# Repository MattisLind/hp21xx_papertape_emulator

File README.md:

# HP 21XX Paper Tape Emulator

The latest hardware version is **V2.0** (V2). V2.0 uses a **full-size SD card** and requires the **V2 enclosure**, which is the latest enclosure revision in [`box/cad`](box/cad). Earlier boards use microSD cards and the earlier enclosure. **Firmware V2.0 requires the V2.0 board** because its activity LED circuit uses active-low drive.

The current repository **HEAD is V2.0**. All V1.1 files, including firmware,
release binaries, PCB design and enclosure, are preserved at the
[`V1.1` Git tag](https://github.com/MattisLind/hp21xx_papertape_emulator/tree/V1.1).
Browse that tag or check it out with `git switch --detach V1.1` to use the
complete V1.1 revision.

The idea to this project come from this page: [newton.freehostia.com/hp](https://newton.freehostia.com/hp/). A simple PIC processor connected to the ubiquitous HP 12566 Microcircuit boards that provide 16 bits of general input and output with a simple handshake. The software interface is identical to the one used for the paper tape reader and paper tape punch. The interface originally used for punch and reader, 12597A is a +12V level interface which made them a bit harder to interface. The 12566A board which used just standard +5V signals was easier to work with and I had plenty of them.

So I thought I should make my own, but then I thought, why involve a PC. I could store the files I wished to download on a small SD-card and have a small display and a couple of buttons to interact with to select what file I wanted to download into the machine! And then there was this idea, why not make it work as a punch as well so that I can take the output from the HP computer and store it on a file that subsequently can be uploaded. Useful if one would try compiling some small program on it.

## Progress

Now I am able to both read files into the computer and punch from the computer. Here is a quick video showing when a Chess program is loaded into my HP 2100S.

Loading of the 72 k abolute binary files takes place when the red LED light up for a few seconds. It fills up the entire 32k Word memory space of the HP 2100.

The photo shows the earlier board with a microSD card; V2 uses a full-size SD card. There are three buttons, Up, Down and Select, and a small 128x64 OLED panel to configure and control it. The USB-C connector can be used to power the device unless powered over the 26 pin ribbon connector. The green LED indicates power and the red LED indicates activity.

The UI is rather simple. Simply navigating up and down and press the select button. The main menu have two menu items, one to select the reader file and one select the punch file. Pressing select will get you to a file selct menu where the currently selected file is shown and where you can navigate to the file you want to select. Pressing select also exits back to the main menu. On the punch menu there are also an option to create a new file with a sequence number. If an existing file is selected it will append to that file.

Since there are only three buttons the UI also have special actions when pressing a button for 2 seconds. A long press on the select menu brings up the configuration menu. In here you can set if signals are active high or active low. For 12566A and 12566B there are two board revsions which get you to choose from active high (POS TRUE) or active low (GND TRUE) data. The active high or low for hand shake signals are configurable on both these cards. The 12566C has all parameters configurable. You should check yoour board so that it matches the config you set in this menu. There is also an option to configure 12V signals or 5V signals. 5V is used for 12566 boards while 12V is used for 12597 boards. You cannot mix a 12566 board and a 12566 board and connect them simultaneously to the paper tape emulator. There are also certain variants of the 12597 board that have -12V signals. This type of board is not supported. Unless you convert the board to +12V.

If you long press on the Down button when in the main menu the currently selected file will be rewound to the beginning so that it can be read again.

If you long press on the Up button the USB MSC mode will be stated and all emulation is stopped. This will allow you to browse the contents from a host computer if the emulator is connected over USB-C. This feature is now active. The STM32F103 have a very small memory and it will take a while for the MCU to transfer big amounts to the host. Unfortunately it seems like at least Windows 10 wants to read about 16000 blocks from the disk when it is mounted. This takes quite some time and will ead to that the drive is not showing up active in the computer. Probably because the file system is 8Gb. I think that by making the partition smaller it will read less from the disk when moounting it. A 32 Meg partition will easily hold all the paper tapes you ever will use on a HP21xx machine.

## BOM

For all the surface mount components the BOM is among the production files in the kicad folder. Other than that the following hardware is needed to complete the emulator:

* [Screws  M2 5mm.  8 pcs](https://www.aliexpress.com/item/32768907028.html)
* [Nylon hex standoffs for the display are 6mm M2. 4 pcs](https://www.aliexpress.com/item/1005003577479911.html)
* [Nylon washers M2 5mm x 1mm high: 8 pcs.](https://www.aliexpress.com/item/1005008318320472.html)
* [Display is a OLED 128x64 with I2C Using SH1106 chip.](https://www.aliexpress.com/item/1005007451015054.html)
* [Buttons are 6x6 mm 13 mm high tactile buttons](https://www.aliexpress.com/item/1005002487399422.html)
* [Connector is Ampehnol FCI 71922-126LF](https://www.mouser.se/ProductDetail/649-71922-126LF)
* Red 5 mm LED
* Green 5 mm LED
* 4 pin header 2.54 mm for SWD and serial debugging port. 2 pcs.

## Connecting it to the HP machine 

The connector for the HP computer is a 48 pin 0.156 inch (3.96 mm) connector. EDAC and Sullins manufacture these.

I used a 26 pin ribbon connector in the emulator end and splitted that one in two 13 conductor halves going to one each 48 pin connector.

### Mods to supply 5V to the emulator

A good idea is to modify the 12566 and 12597 boards to supply 5V to the emulator. There are schottky diodes on the supply line internally on the emulator to avoid backpowering things so it should be safe to connect the punch and reader to different computers and also safe to have a PC connected to the USB simultaneously.

I modifed my 12566 boards to supply 5V on pin 20 since it is unused also on the 12597 boards this pin is unused.

### Reader
|Pin on 26 pin connector | Designator on the 26 pin connector | Pin on 48 pin connector for the 12566 board |HP designator on 12566 board | Pin on the 48 pin connector for the 12597 board | HP designator on 12597 board |
|----|-----|-----|----|----|----|
| 14 | NC  | NA  | NA |    |    |
| 15 | INCR | 22 |  DEVICE COMMAND  | AA  | Read |
| 16 | OUTFR | 23 | DEVICE FLAG | 23 | Feed Hole |
| 17 | OUT7 | 8  | Bit 7 | 8 | Bit 7 | 
| 18 | OUT6 | 7  | Bit 6 | 7 | Bit 6 |
| 19 | OUT5 | 6  | Bit 5 | 6 | Bit 5 | 
| 20 | OUT4 | 5  | Bit 4 | 5 | Bit 4 |
| 21 | OUT3 | 4  | Bit 3 | 4 | Bit 3 |
| 22 | OUT2 | 3  | Bit 2 | 3 | Bit 2 |
| 23 | OUT1 | 2  | Bit 1 | 2 | Bit 1 |
| 24 | OUT0 | 1  | Bit 0 | 1 | Bit 0 |
| 25 | GND  | 24 | Ground | 24 | Ground |
| 26 | +5V  | 20 | | 20 |  |

### Punch

Please note that the table below has been updated since I found errors in the table. If you built this cable already, please doublecheck the cable!

|Pin on 26 pin connector | Designator on the 26 pin connector | Pin on 48 pin connector for the 12566 board | HP designator on 12566 board |Pin on the 48 pin connector for the 12597 board | HP designator on 12597 board| 
|----|-----|-----|----|----|----|
| 1  | +5V | 20  | | 20 |  |
| 2  | GND | 24  | GROUND | 24 | Ground |
| 3  | IN0  | A  | BIT 0 | A  | Bit 0 |
| 4  | IN1  | B  | BIT 1 | B  | Bit 1 |
| 5  | IN2  | C  | BIT 2 | C  | Bit 2|
| 6  | IN3  | D  | BIT 3 | D  | Bit 3 |
| 7  | IN4  | E  | BIT 4 | E  | Bit 4 |
| 8  | IN5  | F  | BIT 5 | F | Bit 5 |
| 9 | IN6  | H  | BIT 6 | H  | Bit 6 |
| 10 | IN7 | J | BIT 7 | J | Bit 7 |
| 11  | OUTFP| 23 | DEVICE FLAG | 23 | Flag |
| 12  | INCP | 22  | DEVICE COMMAND   | AA | Punch |
| 13 | PAPER_LOW | 6 | BIT 5 | 6 | Low Tape|

## Firmware

The firmware is built using the Arduino framework. <strike>I have been using the Maple based core adapted by Roger Clark: [Arduino_STM32](https://github.com/rogerclarkmelbourne/arduino_stm32). Follow the instructins and install this in your Arduino Environment.
In addition to that I have replaced the standard SDfat V2 library with a SDfat library that works with this core, [SDFat library by VictorPV](https://github.com/victorpv/SdFat), but still support long file names.

Then it is important to select this core under tools. Also select the correct target, STM32F103C8.</strike>

I now converted into using the standard core for STM32 on Arduino. The TinyUSB library has to be installed. In addition to that I downloaded and installed [TinyUSB-Arduino-STM32](https://github.com/code-fiasco/TinyUSB-Arduino-STM32?utm_source=chatgpt.com) for STM32 support. Please follow instructions in the repo.

The picture above indicate the config needed. STM32F103 Bluepill. Please adapt dependning on download method. In the binaries folder there is a new binary that can be used directly.

### Building and programming with Docker and Make

Install Docker and Make, then run:

```sh
make setup    # Build the tool image and download its pinned dependencies
make          # Build firmware using the container
make release  # Also copy V2.0 into binaries/
make probe    # Identify the connected ST-Link target
make program  # Back up existing flash, program, verify, and reset into firmware
```

Make selects `linux/amd64`, including on Apple Silicon, because STM32 core
2.11.0's STM32Tools package has no Linux ARM64 release. Docker Desktop supplies
the required emulation. The Dockerfile contains Arduino CLI 1.1.1, the STM32 compiler and core, all
firmware libraries, OpenOCD, and GDB. Build outputs (`.bin`, `.hex`, `.elf`) are
in `build/firmware/`. The release binary is
[`binaries/hp21xx_papertape_emulator.ino.v2.0.bin`](binaries/hp21xx_papertape_emulator.ino.v2.0.bin).

On Linux, programming uses `/dev/bus/usb` directly inside the container. On
macOS, [Docker Desktop cannot directly pass USB devices to containers](https://docs.docker.com/desktop/troubleshoot-and-support/faqs/general/).
Make automatically downloads a checksum-verified native OpenOCD USB bridge into
`build/stlink/`, runs the programming client in Docker, and stops the bridge
when finished. No Arduino or programming-tool installation is needed on the
host. The Mac needs its standard `curl`, `tar`, and `shasum` utilities. The bridge
briefly listens on TCP port 3333 while programming. `make bridge` runs it manually;
`make program PROGRAM_HOST=host.docker.internal` uses an already-running bridge.
An ST-Link attached to another machine can be used via `PROGRAM_HOST=hostname`.

Existing 64 KiB flash contents are saved with a timestamp in `build/stlink/`
before programming. GDB verifies the loaded sections before resetting the MCU.

The build uses the screenshot's BluePill F103C8 settings: STM32 core 2.11.0,
smallest (`-Os`) optimization, Newlib Nano, no debug, USB support None, generic
Serial enabled, low/full USB speed, and OpenOCD STLink (SWD). SdFat uses
`SDFAT_FILE_TYPE=1`, FAT12 support, UTF-8 filenames, and its block-device interface.
USB is provided by the separate TinyUSB STM32 port.

Dependencies are U8g2 2.36.19, Adafruit TinyUSB 3.7.7,
[SdFat 2.3.1](https://github.com/greiman/SdFat/tree/cda057318bec196183d4cc92b01bc1dd64bbfb02)
commit `cda057318bec196183d4cc92b01bc1dd64bbfb02`, and
[TinyUSB-Arduino-STM32](https://github.com/code-fiasco/TinyUSB-Arduino-STM32)
commit `d722701738f48234fd9fb6a4110e7885ef2393da`.

The latest schematic supports SWD programming and factory USART1 programming.
JP1 bridges BOOT0 to 3.3 V; BOOT1/PB2 is held low through the existing PUSEL
pull-down circuit during reset. Bridge JP1 and press the new SW4 reset button
to enter the ROM serial bootloader. A full power cycle also works when no
other connection keeps the board powered. Connect a 3.3 V logic USB–UART
adapter's TX to J2 pin 3, RX to pin 2, and ground to pin 4. Leave J2 pin 1
unconnected when the board is USB powered. Remove the BOOT0 bridge and reset
after programming to run the application. Existing boards may require a
BOOT0 wire and an external reset connection. The committed PCB still needs
updating to match these schematic changes.

Software to upload code via serial port is for example [stm32flash](https://github.com/FYSETC/stm32flash)

I have not tried serial boot mode myself so I cannot tell how to work with it. I always use the STM32 SWD dongle.

The V2.0 board connects D1 to 3.3 V so PC13 sinks its current through
R3 (1 kΩ). Firmware V2.0 uses active-low LED drive: LOW turns the activity LED
on and HIGH turns it off. It requires the V2.0 board; on older boards with
the original active-high LED circuit its indication will be inverted. Use
firmware V1.1 for those earlier boards. See the [schematic review](kicad/hp21xx_papertape_emulator/schematic-review.md)
for component selections, decoupling placement and the JTAG reset pull-up
analysis. R64/R76 now use 2.2 kΩ pull-downs to hold those MOSFET gates low
during reset.

## Software releases

### V2.0

V2.0 requires the V2.0 board with its revised activity LED circuit and full-size
SD socket. It includes active-low activity LED drive and displays `V2.0` in the
menu header. The release binary is
[`hp21xx_papertape_emulator.ino.v2.0.bin`](binaries/hp21xx_papertape_emulator.ino.v2.0.bin).
V2.0 hardware also requires the latest V2 enclosure in [`box/cad`](box/cad).
The container build uses 58,748 bytes of flash and 10,496 bytes of static RAM;
the release binary is 59,064 bytes. This release has been built successfully
but has not yet been tested on the V2.0 board.

### V1.1

V1.1 adds a menu-header version indicator and fixes loading `device.use12V`
from `/ptape.cfg`, so the saved voltage setting is restored after power cycling.
The V1.1 container build uses 58,744 bytes of flash and 10,496 bytes of static
RAM; the release binary is 59,060 bytes. It was programmed into the 64 KiB
STM32 target via ST-Link V2, and all loaded sections passed readback verification.
Hardware testing confirmed the V1.1 menu indicator and that the 12 V selection
is retained after a power cycle.

## Enclosure

I was thinking I should do an enclosure for this little thing, but my skills in FreeCAD wasn't very good. Later I started to use Codex quite a bit and found that it was actually able to do it. Half an hour with Codex and there were a couple of STL-files for an enclosure! A friend test printed them for me and they were a good fit. 

The latest files in [`box/cad`](box/cad) are the **V2 enclosure**, required for the V2 board with its full-size SD card. See the [enclosure documentation](box/cad/README.md) for details.

## Documentation

Here are some links to relevant HP document for the 12597 and 12566 boards:

* [12566B Micro circuit interface manual](https://bitsavers.org/pdf/hp/21xx/interfaces/12566.pdf)
* [12597A-002 Reader interface manual](https://www.bitsavers.org/pdf/hp/21xx/interfaces/12597A-002.pdf)
* [12597A-005 Punch interface manual](https://www.bitsavers.org/pdf/hp/21xx/interfaces/12597A-005.pdf)

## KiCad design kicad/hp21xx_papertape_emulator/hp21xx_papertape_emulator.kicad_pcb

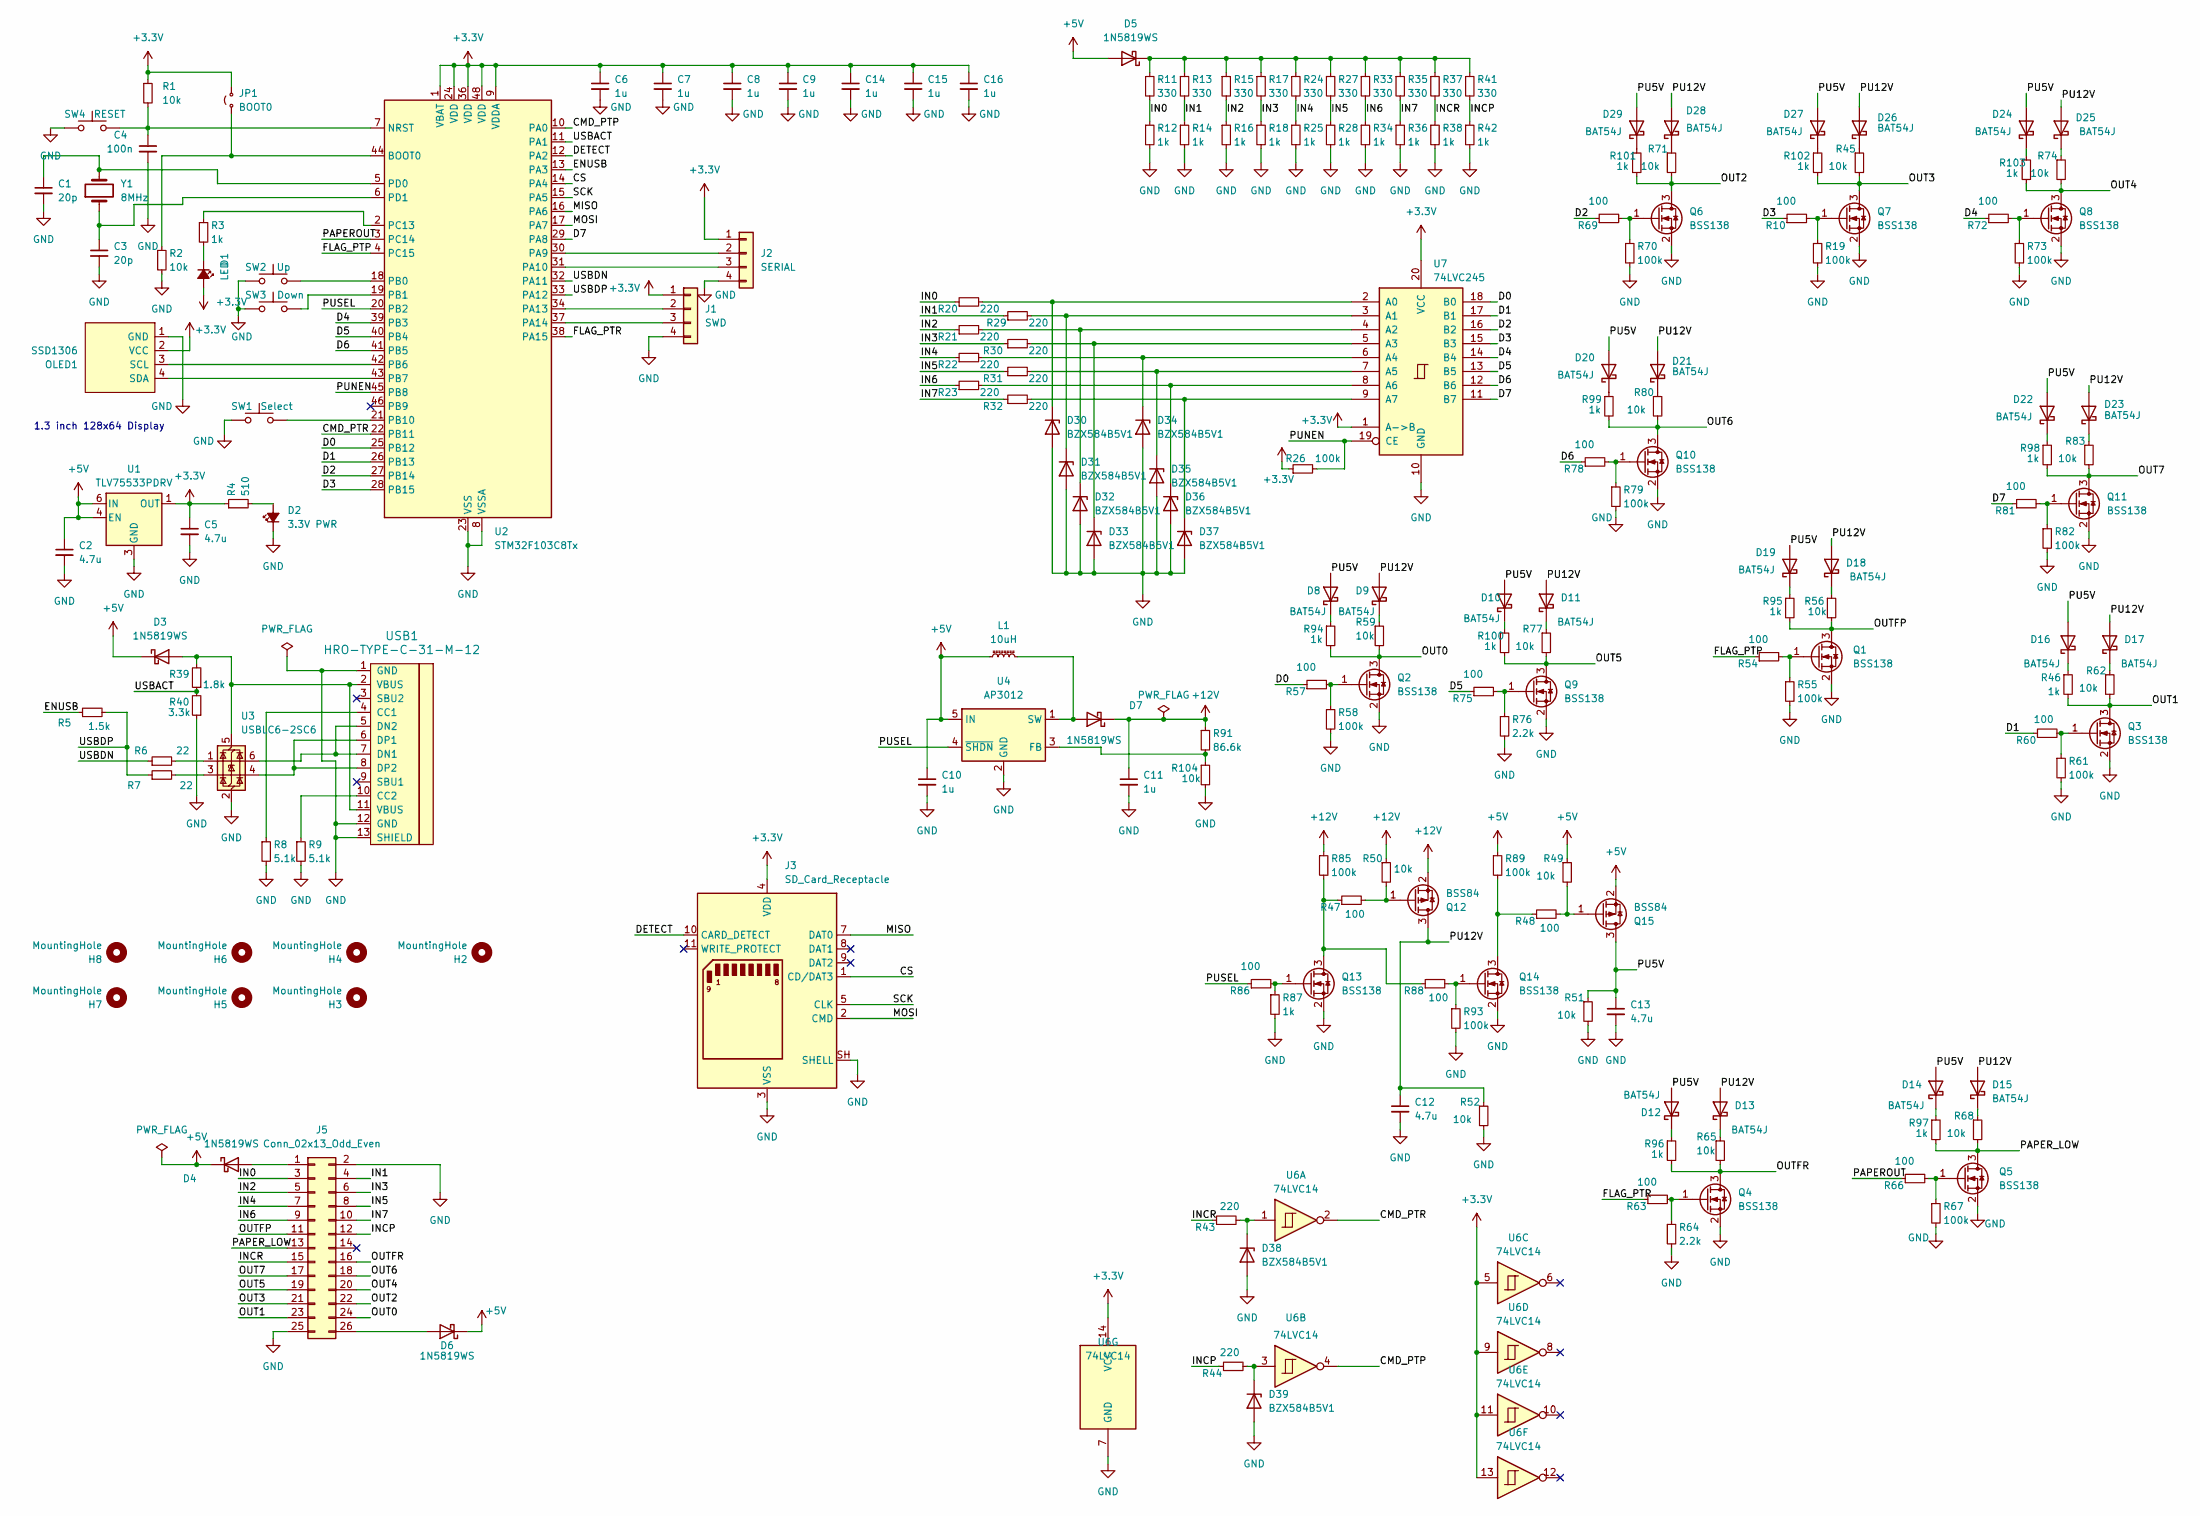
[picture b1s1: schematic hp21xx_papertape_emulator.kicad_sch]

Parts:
C1, C3: 20p; C_0402_1005Metric; LCSC C1554
C2, C5, C12, C13: 4.7u; C_1206_3216Metric; LCSC C29823
C4: 100n; C_0402_1005Metric; LCSC C1525
C6, C7, C8, C9, C14, C15, C16: 1u; C_0402_1005Metric; LCSC C52923
C10, C11: 1u; C_0805_2012Metric; LCSC C28323
D1: LED; LED_D5.0mm
D2: 3.3V PWR; LED_D5.0mm
D3, D4, D5, D6, D7: 1N5819WS; D_SOD-323; LCSC C191023
D8, D9, D10, D11, D12, D13, D14, D15, D16, D17, D18, D19, D20, D21, D22, D23, D24, D25, D26, D27, D28, D29: BAT54J; D_SOD-523; LCSC C51315114
D30, D31, D32, D33, D34, D35, D36, D37, D38, D39: BZX584B5V1; D_SOD-523; LCSC C968173
H2, H4, H6, H8: MountingHole; MountingHole_2.5mm
H3, H5, H7: MountingHole; MountingHole_2.2mm_M2
J1: SWD; PinHeader_1x04_P2.54mm_Vertical
J2: SERIAL; PinHeader_1x04_P2.54mm_Vertical
J3: SD_Card_Receptacle; SD_SHOUHAN_SD-CARD-11P; LCSC C7529393
J5: Conn_02x13_Odd_Even; IDC-Header_2x13_P2.54mm_Latch_Horizontal
JP1: BOOT0; PinHeader_1x02_P2.54mm_Vertical
L1: 10uH; L_Sunlord_SWPA3010S; LCSC C2049730
OLED1: SSD1306; PinHeader_1x04_P2.54mm_Vertical
Q1, Q2, Q3, Q4, Q5, Q6, Q7, Q8, Q9, Q10, Q11, Q13, Q14: BSS138; SOT-23; LCSC C53113928
Q12, Q15: BSS84; SOT-23; LCSC C41354933
R1, R2, R45, R49, R50, R51, R52, R56, R59, R62, R65, R68, R71, R74, R77, R80, R83, R104: 10k; R_0402_1005Metric; LCSC C25744
R3, R12, R14, R16, R18, R25, R28, R34, R36, R38, R42, R46, R87, R94, R95, R96, R97, R98, R99, R100, R101, R102, R103: 1k; R_0402_1005Metric; LCSC C11702
R4: 510; R_0402_1005Metric; LCSC C25123
R5: 1.5k; R_0402_1005Metric; LCSC C25867
R6, R7: 22; R_0402_1005Metric; LCSC C25092
R8, R9: 5.1k; R_0402_1005Metric; LCSC C25905
R10, R47, R48, R54, R57, R60, R63, R66, R69, R72, R75, R78, R81, R86, R88: 100; R_0402_1005Metric; LCSC C25076
R11, R13, R15, R17, R24, R27, R33, R35, R37, R41: 330; R_0805_2012Metric; LCSC C17630
R19, R26, R55, R58, R61, R67, R70, R73, R79, R82, R85, R89, R93: 100k; R_0402_1005Metric; LCSC C25741
R20, R21, R22, R23, R29, R30, R31, R32, R43, R44: 220; R_0402_1005Metric; LCSC C427205
R39: 1.8k; R_0603_1608Metric; LCSC C4177
R40: 3.3k; R_0402_1005Metric; LCSC C25890
R64, R76: 2.2k; R_0402_1005Metric; LCSC C25879
R91: 86.6k; R_0402_1005Metric; LCSC C19709
SW1: Select; SW_PUSH_6mm_H13mm
SW2: Up; SW_PUSH_6mm_H13mm
SW3: Down; SW_PUSH_6mm_H13mm
SW4: RESET; SW_SPST_TS-1088-xR020; LCSC C720477
U1: TLV75533PDRV; WSON-6-1EP_2x2mm_P0.65mm_EP1x1.6mm; LCSC C2861750
U2: STM32F103C8Tx; LQFP-48_7x7mm_P0.5mm; LCSC C8734
U3: USBLC6-2SC6; SOT-23-6; LCSC C21713975
U4: AP3012; SOT-23-5; LCSC C102618
U6: 74LVC14; TSSOP-14_4.4x5mm_P0.65mm; LCSC C7663
U7: 74LVC245; TSSOP-20_4.4x6.5mm_P0.65mm; LCSC C7848
USB1: HRO-TYPE-C-31-M-12; MPN TYPE-C-31-M-12; LCSC C165948
Y1: 8MHz; Crystal_SMD_5032-2Pin_5.0x3.2mm; LCSC C115962

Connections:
+3.3V: C5.1, C6.1, C7.1, C8.1, C9.1, C14.1, C15.1, C16.1, D1.2 (A), J1.1, J2.1, J3.4 (VDD), JP1.2 (B), OLED1.2 (VCC), R1.1, R4.1, R26.1, U1.1 (OUT), U2.1 (VBAT), U2.9 (VDDA), U2.24 (VDD), U2.36 (VDD), U2.48 (VDD), U6.5, U6.9, U6.11, U6.13, U6.14 (VCC), U7.1 (A->B), U7.20 (VCC)
+5V: C2.1, C10.1, D3.1 (K), D4.1 (K), D5.2 (A), D6.1 (K), L1.1, Q15.2 (S), R49.1, R89.1, U1.4 (EN), U1.6 (IN), U4.5 (IN)
+12V: C11.1, D7.1 (K), Q12.2 (S), R50.1, R85.1, R91.1
/CMD_PTP: U2.10 (PA0), U6.4
/CMD_PTR: U2.22 (PB11), U6.2
/CS: J3.1 (CD/DAT3), U2.14 (PA4)
/D0: R57.1, U2.25 (PB12), U7.18 (B0)
/D1: R60.1, U2.26 (PB13), U7.17 (B1)
/D2: R69.1, U2.27 (PB14), U7.16 (B2)
/D3: R10.1, U2.28 (PB15), U7.15 (B3)
/D4: R72.1, U2.39 (PB3), U7.14 (B4)
/D5: R75.1, U2.40 (PB4), U7.13 (B5)
/D6: R78.1, U2.41 (PB5), U7.12 (B6)
/D7: R81.1, U2.29 (PA8), U7.11 (B7)
/DETECT: J3.10 (CARD_DETECT), U2.12 (PA2)
/ENUSB: R5.1, U2.13 (PA3)
/FLAG_PTP: R54.1, U2.4 (PC15)
/FLAG_PTR: R63.1, U2.38 (PA15)
/IN0: J5.3, R11.2, R12.1, R20.1
/IN1: J5.4, R13.2, R14.1, R29.1
/IN2: J5.5, R15.2, R16.1, R21.1
/IN3: J5.6, R17.2, R18.1, R30.1
/IN4: J5.7, R22.1, R24.2, R25.1
/IN5: J5.8, R27.2, R28.1, R31.1
/IN6: J5.9, R23.1, R33.2, R34.1
/IN7: J5.10, R32.1, R35.2, R36.1
/INCP: J5.12, R41.2, R42.1, R44.1
/INCR: J5.15, R37.2, R38.1, R43.1
/MISO: J3.7 (DAT0), U2.16 (PA6)
/MOSI: J3.2 (CMD), U2.17 (PA7)
/OUT0: J5.24, Q2.3 (D), R59.2, R94.2
/OUT1: J5.23, Q3.3 (D), R46.2, R62.2
/OUT2: J5.22, Q6.3 (D), R71.2, R101.2
/OUT3: J5.21, Q7.3 (D), R45.2, R102.2
/OUT4: J5.20, Q8.3 (D), R74.2, R103.2
/OUT5: J5.19, Q9.3 (D), R77.2, R100.2
/OUT6: J5.18, Q10.3 (D), R80.2, R99.2
/OUT7: J5.17, Q11.3 (D), R83.2, R98.2
/OUTFP: J5.11, Q1.3 (D), R56.2, R95.2
/OUTFR: J5.16, Q4.3 (D), R65.2, R96.2
/PAPEROUT: R66.1, U2.3 (PC14)
/PAPER_LOW: J5.13, Q5.3 (D), R68.2, R97.2
/PU5V: C13.1, D8.2 (A), D10.2 (A), D12.2 (A), D14.2 (A), D16.2 (A), D19.2 (A), D20.2 (A), D22.2 (A), D24.2 (A), D27.2 (A), D29.2 (A), Q15.3 (D), R51.1
/PU12V: C12.1, D9.2 (A), D11.2 (A), D13.2 (A), D15.2 (A), D17.2 (A), D18.2 (A), D21.2 (A), D23.2 (A), D25.2 (A), D26.2 (A), D28.2 (A), Q12.3 (D), R52.1
/PUNEN: R26.2, U2.45 (PB8), U7.19 (CE)
/PUSEL: R86.1, U2.20 (PB2), U4.4 (~SHDN)
/SCK: J3.5 (CLK), U2.15 (PA5)
/USBACT: R39.1, R40.2, U2.11 (PA1)
/USBDN: R6.1, U2.32 (PA11)
/USBDP: R5.2, R7.1, U2.33 (PA12)
GND: C1.2, C2.2, C3.2, C4.2, C5.2, C6.2, C7.2, C8.2, C9.2, C10.2, C11.2, C12.2, C13.2, C14.2, C15.2, C16.2, D2.1 (K), D30.2 (A), D31.2 (A), D32.2 (A), D33.2 (A), D34.2 (A), D35.2 (A), D36.2 (A), D37.2 (A), D38.2 (A), D39.2 (A), J1.4, J2.4, J3.3 (VSS), J3.6 (VSS), J3.SH (SHELL), J5.2, J5.25, OLED1.1 (GND), Q1.2 (S), Q2.2 (S), Q3.2 (S), Q4.2 (S), Q5.2 (S), Q6.2 (S), Q7.2 (S), Q8.2 (S), Q9.2 (S), Q10.2 (S), Q11.2 (S), Q13.2 (S), Q14.2 (S), R2.2, R8.2, R9.2, R12.2, R14.2, R16.2, R18.2, R19.2, R25.2, R28.2, R34.2, R36.2, R38.2, R40.1, R42.2, R51.2, R52.2, R55.2, R58.2, R61.2, R64.2, R67.2, R70.2, R73.2, R76.2, R79.2, R82.2, R87.2, R93.2, R104.2, SW1.1, SW2.1, SW3.1, SW4.1, U1.3 (GND), U1.7 (GND), U2.8 (VSSA), U2.23 (VSS), U2.35 (VSS), U2.47 (VSS), U3.2 (GND), U4.2 (GND), U6.7 (GND), U7.10 (GND), USB1.1 (GND), USB1.12 (GND), USB1.13 (SHIELD)
unnamed: D1.1 (K), R3.2
unnamed: D2.2 (A), R4.2
unnamed: D3.2 (A), R39.2, U3.5 (VBUS), USB1.2 (VBUS), USB1.11 (VBUS)
unnamed: D4.2 (A), J5.1
unnamed: D5.1 (K), R11.1, R13.1, R15.1, R17.1, R24.1, R27.1, R33.1, R35.1, R37.1, R41.1
unnamed: D6.2 (A), J5.26
unnamed: D7.2 (A), L1.2, U4.1 (SW)
unnamed: D8.1 (K), R94.1
unnamed: D9.1 (K), R59.1
unnamed: D10.1 (K), R100.1
unnamed: D11.1 (K), R77.1
unnamed: D12.1 (K), R96.1
unnamed: D13.1 (K), R65.1
unnamed: D14.1 (K), R97.1
unnamed: D15.1 (K), R68.1
unnamed: D16.1 (K), R46.1
unnamed: D17.1 (K), R62.1
unnamed: D18.1 (K), R56.1
unnamed: D19.1 (K), R95.1
unnamed: D20.1 (K), R99.1
unnamed: D21.1 (K), R80.1
unnamed: D22.1 (K), R98.1
unnamed: D23.1 (K), R83.1
unnamed: D24.1 (K), R103.1
unnamed: D25.1 (K), R74.1
unnamed: D26.1 (K), R45.1
unnamed: D27.1 (K), R102.1
unnamed: D28.1 (K), R71.1
unnamed: D29.1 (K), R101.1
unnamed: D30.1 (K), R20.2, U7.2 (A0)
unnamed: D31.1 (K), R29.2, U7.3 (A1)
unnamed: D32.1 (K), R21.2, U7.4 (A2)
unnamed: D33.1 (K), R30.2, U7.5 (A3)
unnamed: D34.1 (K), R22.2, U7.6 (A4)
unnamed: D35.1 (K), R31.2, U7.7 (A5)
unnamed: D36.1 (K), R23.2, U7.8 (A6)
unnamed: D37.1 (K), R32.2, U7.9 (A7)
unnamed: D38.1 (K), R43.2, U6.1
unnamed: D39.1 (K), R44.2, U6.3
unnamed: J1.2, U2.34 (PA13)
unnamed: J1.3, U2.37 (PA14)
unnamed: J2.2, U2.30 (PA9)
unnamed: J2.3, U2.31 (PA10)
unnamed: JP1.1 (A), R2.1, U2.44 (BOOT0)
unnamed: OLED1.3 (SCL), U2.42 (PB6)
unnamed: OLED1.4 (SDA), U2.43 (PB7)
unnamed: Q1.1 (G), R54.2, R55.1
unnamed: Q2.1 (G), R57.2, R58.1
unnamed: Q3.1 (G), R60.2, R61.1
unnamed: Q4.1 (G), R63.2, R64.1
unnamed: Q5.1 (G), R66.2, R67.1
unnamed: Q6.1 (G), R69.2, R70.1
unnamed: Q7.1 (G), R10.2, R19.1
unnamed: Q8.1 (G), R72.2, R73.1
unnamed: Q9.1 (G), R75.2, R76.1
unnamed: Q10.1 (G), R78.2, R79.1
unnamed: Q11.1 (G), R81.2, R82.1
unnamed: Q12.1 (G), R47.2, R50.2
unnamed: Q13.3 (D), R47.1, R85.2, R88.1
unnamed: Q13.1 (G), R86.2, R87.1
unnamed: Q14.3 (D), R48.1, R89.2
unnamed: Q14.1 (G), R88.2, R93.1
unnamed: Q15.1 (G), R48.2, R49.2
unnamed: R6.2, U3.1 (I/O1)
unnamed: R7.2, U3.3 (I/O2)
unnamed: C4.1, R1.2, SW4.2, U2.7 (NRST)
unnamed: SW2.2, U2.18 (PB0)
unnamed: SW3.2, U2.19 (PB1)
unnamed: SW1.2, U2.21 (PB10)
unnamed: R3.1, U2.2 (PC13)
unnamed: C1.1, U2.5 (PD0), Y1.2
unnamed: C3.1, U2.6 (PD1), Y1.1
unnamed: R91.2, R104.1, U4.3 (FB)
unnamed: R8.1, USB1.4 (CC1)
unnamed: R9.1, USB1.10 (CC2)
unnamed: U3.6 (I/O1), USB1.5 (DN2), USB1.7 (DN1)
unnamed: U3.4 (I/O2), USB1.6 (DP1), USB1.8 (DP2)

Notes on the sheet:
1.3 inch 128x64 Display

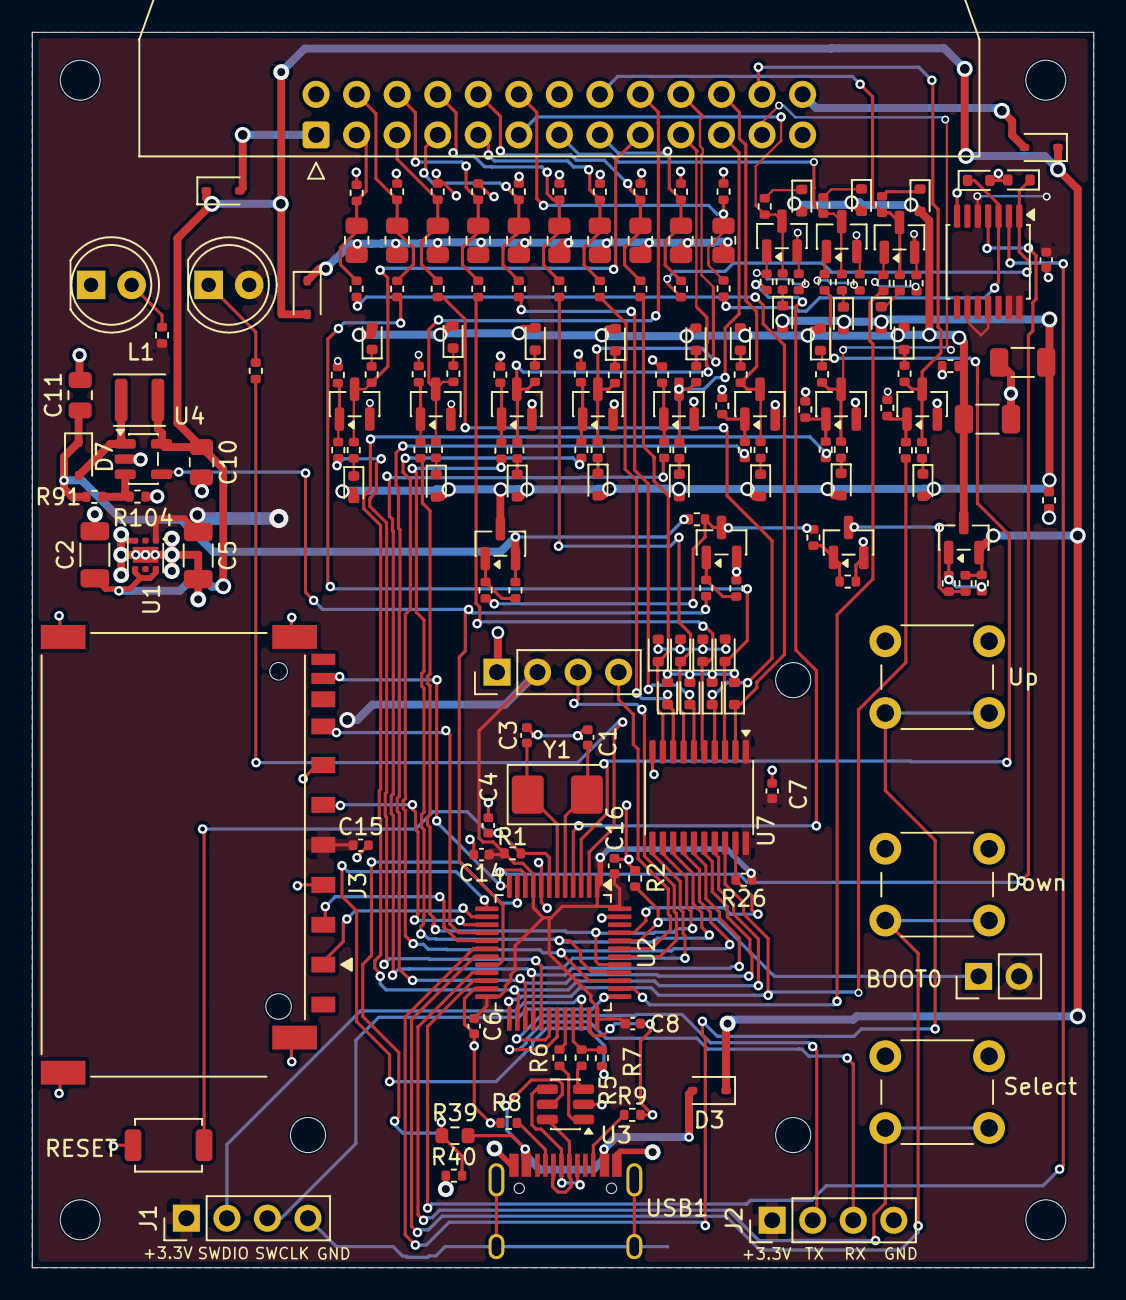
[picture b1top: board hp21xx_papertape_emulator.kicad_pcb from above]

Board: 2 copper layers, 66.5 x 77.4 mm, 196 parts (0 on the bottom side), 128 nets.

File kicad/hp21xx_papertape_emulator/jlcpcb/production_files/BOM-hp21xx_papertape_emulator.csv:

Comment,Designator,Footprint,LCSC,Quantity
1.5k,R5,R_0402_1005Metric,C25867,1
1.8k,R39,R_0603_1608Metric,C4177,1
100,"R10,R47,R48,R54,R57,R60,R63,R66,R69,R72,R75,R78,R81,R86,R88",R_0402_1005Metric,C25076,15
100k,"R19,R26,R55,R58,R61,R67,R70,R73,R79,R82,R85,R89,R93",R_0402_1005Metric,C25741,13
100n,C4,C_0402_1005Metric,C1525,1
10k,"R1,R104,R2,R45,R49,R50,R51,R52,R56,R59,R62,R65,R68,R71,R74,R77,R80,R83",R_0402_1005Metric,C25744,18
10uH,L1,L_Sunlord_SWPA3010S,C2049730,1
1N5819WS,"D3,D4,D5,D6,D7",D_SOD-323,C191023,5
1k,"R100,R101,R102,R103,R12,R14,R16,R18,R25,R28,R3,R34,R36,R38,R42,R46,R87,R94,R95,R96,R97,R98,R99",R_0402_1005Metric,C11702,23
1u,"C10,C11",C_0805_2012Metric,C28323,2
1u,"C14,C15,C16,C6,C7,C8,C9",C_0402_1005Metric,C52923,7
2.2k,"R64,R76",R_0402_1005Metric,C25879,2
20p,"C1,C3",C_0402_1005Metric,C1554,2
22,"R6,R7",R_0402_1005Metric,C25092,2
220,"R20,R21,R22,R23,R29,R30,R31,R32,R43,R44",R_0402_1005Metric,C25091,10
3.3k,R40,R_0402_1005Metric,C25890,1
330,"R11,R13,R15,R17,R24,R27,R33,R35,R37,R41",R_0805_2012Metric,C17630,10
4.7u,"C12,C13,C2,C5",C_1206_3216Metric,C29823,4
5.1k,"R8,R9",R_0402_1005Metric,C25905,2
510,R4,R_0402_1005Metric,C25123,1
74LVC14,U6,TSSOP-14_4.4x5mm_P0.65mm,C7663,1
74LVC245,U7,TSSOP-20_4.4x6.5mm_P0.65mm,C7848,1
86.6k,R91,R_0402_1005Metric,C19709,1
8MHz,Y1,Crystal_SMD_5032-2Pin_5.0x3.2mm,C115962,1
AP3012,U4,SOT-23-5,C102618,1
BAT54J,"D10,D11,D12,D13,D14,D15,D16,D17,D18,D19,D20,D21,D22,D23,D24,D25,D26,D27,D28,D29,D8,D9",D_SOD-523,C51315114,22
BSS138,"Q1,Q10,Q11,Q13,Q14,Q2,Q3,Q4,Q5,Q6,Q7,Q8,Q9",SOT-23,C53113928,13
BSS84,"Q12,Q15",SOT-23,C82079,2
BZX584B5V1,"D30,D31,D32,D33,D34,D35,D36,D37,D38,D39",D_SOD-523,C968173,10
HRO-TYPE-C-31-M-12,USB1,HRO-TYPE-C-31-M-12,C165948,1
RESET,SW4,SW_SPST_TS-1088-xR020,C720477,1
SD_Card_Receptacle,J3,SD_SHOUHAN_SD-CARD-11P,C7529393,1
STM32F103C8Tx,U2,LQFP-48_7x7mm_P0.5mm,C8734,1
TLV75533PDRV,U1,WSON-6-1EP_2x2mm_P0.65mm_EP1x1.6mm,C2861750,1
USBLC6-2SC6,U3,SOT-23-6,C21713975,1

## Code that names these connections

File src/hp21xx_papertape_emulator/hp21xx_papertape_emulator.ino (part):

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  - This is a first complete firmware structure based on the supplied requirements.
  - USB MSC uses TinyUSB/Adafruit TinyUSB style callbacks.
  - All timing-critical paper tape handshakes avoid Serial printing and GUI updates.
  - JTAG is disabled in setup() so PA15, PB3 and PB4 can be used as GPIO.
*/

#include <Arduino.h>
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// Pin mapping from requirements
// -----------------------------------------------------------------------------

static const uint8_t PIN_BTN_UP      = PB0;
static const uint8_t PIN_BTN_DOWN    = PB1;
static const uint8_t PIN_BTN_SELECT  = PB10;

static const uint8_t PIN_SD_CS       = PA4;
static const uint8_t PIN_SD_DETECT   = PA2;  // Active low, pull-up required

static const uint8_t PIN_USB_VBUS    = PA1;  // High when USB VBUS is present
static const uint8_t PIN_USB_PULLUP  = PA3;  // Drive high to connect USB pull-up circuit

static const uint8_t PIN_ACTIVITY_LED = PC13;

static const uint8_t PIN_BUS_DIR      = PB8;  // Active low: low enables external host-to-device buffer for punch input
static const uint8_t PIN_LEVEL_SELECT = PB2;  // High = 12 V interface, Low = 5 V interface
static const uint8_t PIN_OUT_OF_TAPE  = PC14;

static const uint8_t PIN_READER_CMD   = PB11;
static const uint8_t PIN_READER_ACK   = PA15;

static const uint8_t PIN_PUNCH_CMD    = PA0;
static const uint8_t PIN_PUNCH_ACK    = PC15;

static const uint8_t DATA_PINS[8] = {
  PB12, // D0
  PB13, // D1
  PB14, // D2
  PB15, // D3
  PB3,  // D4, requires JTAG disabled
  PB4,  // D5, requires JTAG disabled
  PB5,  // D6
  PA8   // D7
};

// -----------------------------------------------------------------------------
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// Display
// -----------------------------------------------------------------------------

// SH1106 128x64 over hardware I2C on PB6/PB7 for STM32F103 I2C1.
U8G2_SH1106_128X64_NONAME_F_HW_I2C display(U8G2_R0, U8X8_PIN_NONE);

// -----------------------------------------------------------------------------
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}

static void blinkActivity(void) {
  // Revised board: PC13 sinks current through D1/R3; LOW turns the LED on.
  digitalWrite(PIN_ACTIVITY_LED, LOW);
  activityLedOffAtMs = millis() + 1;
}
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
static bool beginSdFilesystem(void) {
  // Configure SPI pins for Arduino_Core_STM32 before starting SdFat.
  SPI.setSCLK(PA5);
  SPI.setMISO(PA6);
  SPI.setMOSI(PA7);
  SPI.begin();

  // Initialize the SD card and FAT filesystem using the selected chip select.
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  }

  // Configure the MSC device once. Later mode switches only toggle unit-ready
  // and the external USB connect circuit on PA3.
  if (!usbMscConfigured) {
    usb_msc.setID("HP21XX", "PaperTapeSD", "1.0");
    usb_msc.setReadWriteCallback(usbMscReadCallback, usbMscWriteCallback, usbMscFlushCallback);
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  usbMscReadCount = 0;
  usbMscWriteCount = 0;

  // Pull up PA3 to enable the external USB connect circuit described in the spec.
  digitalWrite(PIN_USB_PULLUP, HIGH);
  delay(100);

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// -----------------------------------------------------------------------------

static void disableJtagKeepSwd(void) {
  // Free PA15, PB3 and PB4 while keeping SWD on PA13/PA14.
  // Arduino_Core_STM32 uses STM32 HAL macros instead of Maple/libmaple calls.
#if defined(STM32F1xx)
  __HAL_RCC_AFIO_CLK_ENABLE();
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}

void setup(void) {
  // Disable JTAG before configuring PA15/PB3/PB4 as GPIO.
  disableJtagKeepSwd();

  pinMode(PIN_BTN_UP, INPUT_PULLUP);
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  setDefaultConfig();

  // Configure I2C display pins for Arduino_Core_STM32.
  Wire.setSCL(PB6);
  Wire.setSDA(PB7);
  Wire.begin();

  // Initialize I2C display.
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
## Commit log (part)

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2026-01-11 Added schematics.
2026-01-11 Add STM32F103C8 Paper Tape Emulator code
    This commit introduces the STM32F103C8 Paper Tape Emulator for HP 12566, implementing USB MSC and SD card functionalities. Key updates include pin configurations for USB pull-up and SD card detection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
2026-01-16 Tried to create production files but it failed...
2026-01-17 Almost done. Waiting for confirming OLED display and buttons dimensions.
2026-01-17 Update README with project details and functionality
    Expanded project description and clarified functionality.
2026-01-19 Added paper out handling.
2026-01-19 Updated pdf file.
2026-01-23 Updates to support simultaneous PTR and PTP. Able yo use 540 and 541 instead of 245 if not available.
2026-01-24 Updated to use NMOS drivers instead.
2026-01-25 Removed the enable function since it wasn't a good idea.
2026-01-29 New drivers.
2026-01-30 Fixed issues.
2026-01-30 Fixed problems with net unconnected.
2026-01-30 Updated pdf as well.
2026-03-04 spin 2
2026-03-21 Fixed new spin.
2026-03-23 Fixed missing LCSC number for BAT54
2026-05-31 New version
    Completely new version that compiles and starts. Now we need to see if it does the right thing...
2026-06-02 Fixing so that it isn't locking up. Adding debuging
    Fixing so that it isn't locking up. Adding debuging
2026-06-02 Added long press on DOWN
    to reopen file
2026-06-07 Reader works
    Now seems to work. More testing needed
2026-06-10 Fixing puncing
2026-06-12 Picture of the gadget
2026-06-12 Enhance README with detailed emulator information
    Expanded the README with detailed information about the emulator's UI, BOM, connectors, and modifications for supplying 5V.
2026-06-12 Add project progress details and media links to README
    Added a progress section detailing the current capabilities of the project, including reading and punching files. Included a video link and images of the finished board.
2026-06-12 Update README with connector pin mappings
    Added detailed pin mapping for 26 pin to 48 pin connectors for both reader and punch components.
2026-06-12 Revise pin connection details in README
    Updated pin mapping details for 12566 and 12597 boards, including designators and modifications.
2026-06-12 Add documentation section to README
    Added documentation links for HP 12597 and 12566 boards.
2026-06-12 Clarify pin descriptions in README.md
2026-06-14 Document firmware setup and requirements
    Added firmware section detailing the Arduino framework and STM32 setup.
2026-06-14 Fix typos and enhance firmware documentation
    Corrected typos and improved clarity in firmware section.
2026-06-15 Update README with boot mode instructions and details
    Clarified instructions for entering serial boot mode and updated details about the BOOT1 pin.
2026-06-15 Getting punching to work
2026-06-15 Create hp21xx_papertape_emulator.ino.v0.01.bin
    Adding a binary
2026-06-16 Added jumper to be able to use serial bootstrap mode.
2026-06-16 Update README with BOOT0 jumper layout details
    Added information about new layout for BOOT0 jumper.
2026-06-16 New code using new library and TinyUSB
2026-06-16 Added Arduino config picture
2026-06-18 Enhance README with USB and firmware details
    Updated README with detailed instructions on USB MSC mode, firmware setup, and new layout changes.
